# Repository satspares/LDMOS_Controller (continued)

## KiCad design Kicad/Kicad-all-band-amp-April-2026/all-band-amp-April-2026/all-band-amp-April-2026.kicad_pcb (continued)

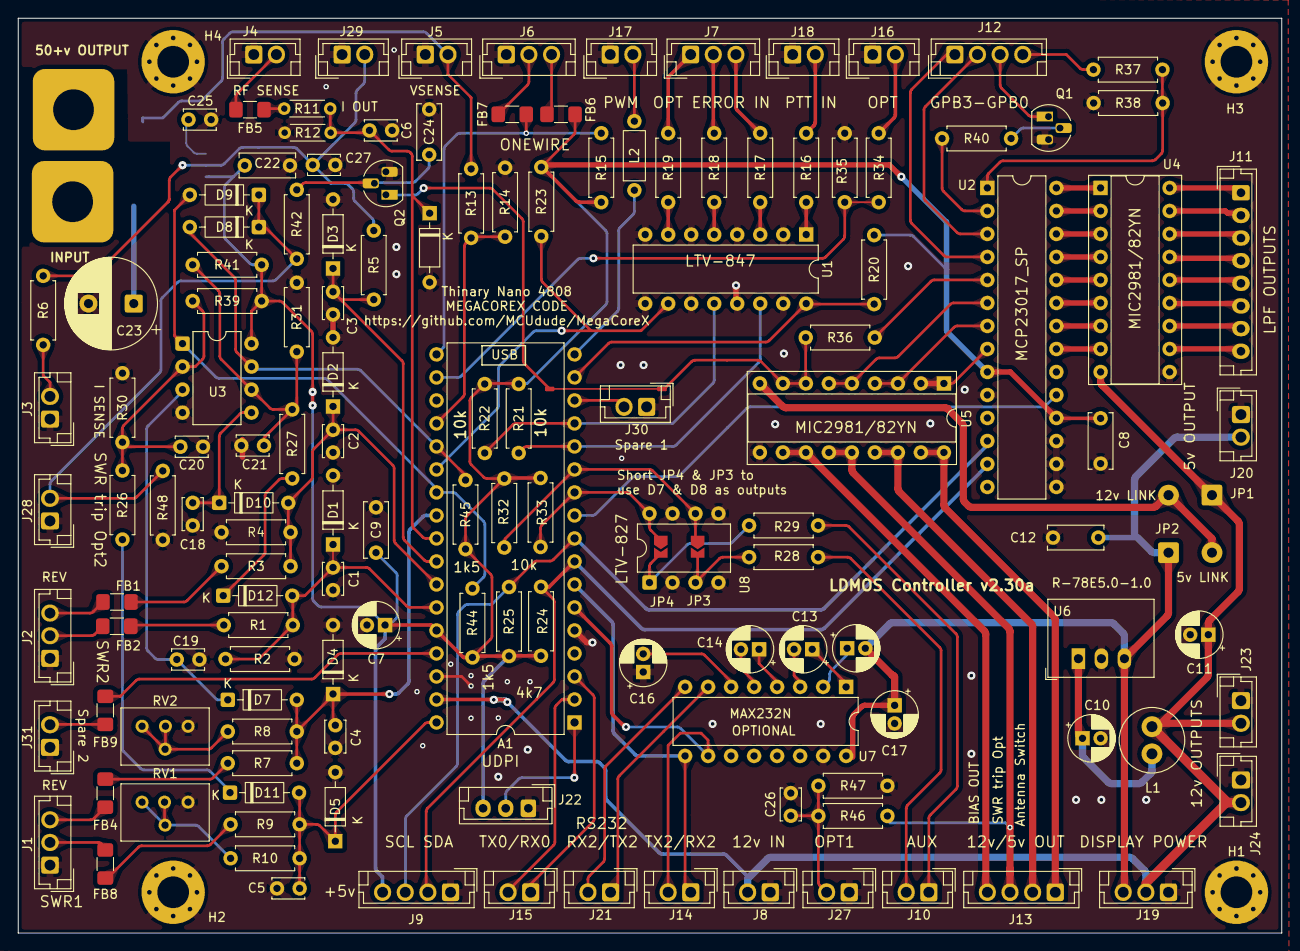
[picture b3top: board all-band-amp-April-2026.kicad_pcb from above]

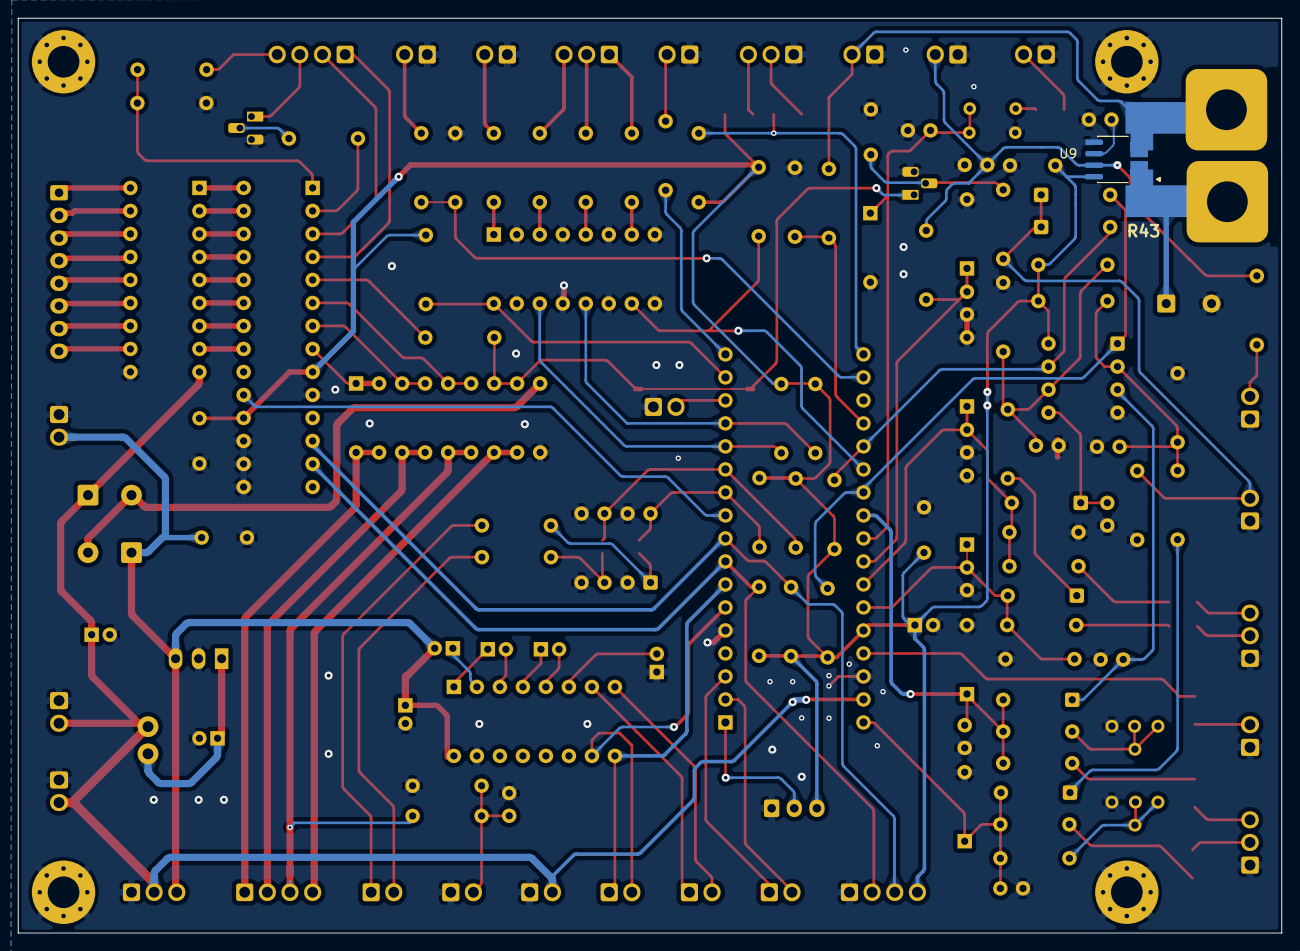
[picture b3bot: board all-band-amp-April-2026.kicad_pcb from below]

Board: 2 copper layers, 139.5 x 101.0 mm, 150 parts (2 on the bottom side), 117 nets.

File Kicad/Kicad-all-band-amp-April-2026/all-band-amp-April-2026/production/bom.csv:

Designator,Footprint,Quantity,Value,LCSC Part #
A1,DIP-34_W15.24mm,1,Arduino_Nano_Every-4808,
"C1, C18, C19, C2, C20, C21, C25, C26, C27, C3, C4, C5, C6",C_Disc_D3.4mm_W2.1mm_P2.50mm,13,10nf,
"C10, C17",CP_Radial_D5.0mm_P2.00mm,2,2.2uf,
"C11, C7",CP_Radial_D5.0mm_P2.00mm,2,10uf,
"C12, C22, C24, C8, C9",C_Disc_D6.0mm_W2.5mm_P5.00mm,5,100nf,
"C13, C14, C15, C16",CP_Radial_D5.0mm_P2.00mm,4,1uf,
C23,CP_Radial_D10.0mm_P5.00mm,1,10uf-220uf,
"D1, D2, D3, D4, D5, D6",D_DO-35_SOD27_P7.62mm_Horizontal,6,Zener 4.7v,
"D10, D11, D12, D7, D8, D9",D_DO-35_SOD27_P7.62mm_Horizontal,6,BAT85,
"FB1, FB2, FB4, FB5, FB6, FB7, FB8, FB9",1206,8,Ferrite,
J1,JST_EH_B3B-EH-A_1x03_P2.50mm_Vertical-mod2,1,SWR1,
J10,JST_EH_B2B-EH-A_1x02_P2.50mm_Vertical-Mod,1,Aux In,
J11,JST_EH_B8B-EH-A_1x08_P2.50mm_Vertical,1,LPF,
J12,JST_EH_B4B-EH-A_1x04_P2.50mm_Vertical-mod2,1,Digi In/Out,
J13,JST_EH_B4B-EH-A_1x04_P2.50mm_Vertical-mod2,1,12v/5v Outputs,
J14,JST_EH_B2B-EH-A_1x02_P2.50mm_Vertical-Mod,1,TX2/RX2,
J15,JST_EH_B2B-EH-A_1x02_P2.50mm_Vertical-Mod,1,TX0/RX0,
"J16, J5",JST_EH_B2B-EH-A_1x02_P2.50mm_Vertical-Mod,2,50v In.,
J17,JST_EH_B2B-EH-A_1x02_P2.50mm_Vertical-Mod,1,PWM Out,
J18,JST_EH_B2B-EH-A_1x02_P2.50mm_Vertical-Mod,1,PTT IN,
J19,JST_EH_B3B-EH-A_1x03_P2.50mm_Vertical-mod2,1,DISPLAY POWER,
J2,JST_EH_B3B-EH-A_1x03_P2.50mm_Vertical-mod2,1,SWR2,
J20,JST_EH_B2B-EH-A_1x02_P2.50mm_Vertical-Mod,1,5V Output,
J21,JST_EH_B2B-EH-A_1x02_P2.50mm_Vertical-Mod,1,RS232,
J22,JST_EH_B3B-EH-A_1x03_P2.50mm_Vertical,1,UDPI,
"J23, J24",JST_EH_B2B-EH-A_1x02_P2.50mm_Vertical-Mod,2,12v Output,
"J27, J28, J29, J30, J31",JST_EH_B2B-EH-A_1x02_P2.50mm_Vertical-Mod,5,SWR trip out,
J3,JST_EH_B2B-EH-A_1x02_P2.50mm_Vertical-Mod,1,I opt Input,
J4,JST_EH_B2B-EH-A_1x02_P2.50mm_Vertical-Mod,1,RF In Level,
J6,JST_EH_B3B-EH-A_1x03_P2.50mm_Vertical-mod2,1,Temp,
J7,JST_EH_B3B-EH-A_1x03_P2.50mm_Vertical-mod2,1,Conn_01x03_Pin,
J8,JST_EH_B2B-EH-A_1x02_P2.50mm_Vertical-Mod,1,12v Input,
J9,JST_EH_B4B-EH-A_1x04_P2.50mm_Vertical-mod2,1,I2c Output,
JP1,SolderWire-0.5sqmm_1x02_P4.8mm_D0.9mm_OD2.3mm,1,Jumper 12v,
JP2,SolderWire-0.5sqmm_1x02_P4.8mm_D0.9mm_OD2.3mm,1,Jumper 5v,
"JP3, JP4",SolderJumper-2_P1.3mm_Open_TrianglePad1.0x1.5mm,2,Jumper_2_Open,
L1,L_Radial_D7.0mm_P3.00mm,1,68uh,
L2,L_Axial_L5.3mm_D2.2mm_P7.62mm_Horizontal_Vishay_IM-1,1,560uh,
"Q1, Q2",TO-92_HandSolder,2,2n2222,
"R1, R44, R45, R46, R9",R_Axial_DIN0207_L6.3mm_D2.5mm_P7.62mm_Horizontal,5,1k5,
"R10, R8",R_Axial_DIN0207_L6.3mm_D2.5mm_P7.62mm_Horizontal,2,100r,
R11,R_Axial_DIN0204_L3.6mm_D1.6mm_P5.08mm_Horizontal,1,4k7,
R12,R_Axial_DIN0204_L3.6mm_D1.6mm_P5.08mm_Horizontal,1,470r,
R13,R_Axial_DIN0207_L6.3mm_D2.5mm_P7.62mm_Horizontal,1,100k,
R14,R_Axial_DIN0207_L6.3mm_D2.5mm_P7.62mm_Horizontal,1,5k1,
"R15, R24, R25",R_Axial_DIN0207_L6.3mm_D2.5mm_P7.62mm_Horizontal,3,4k7,
"R16, R42",R_Axial_DIN0207_L6.3mm_D2.5mm_P7.62mm_Horizontal,2,2k2,
"R17, R18, R19",R_Axial_DIN0207_L6.3mm_D2.5mm_P7.62mm_Horizontal,3,10r,
"R2, R4",R_Axial_DIN0207_L6.3mm_D2.5mm_P7.62mm_Horizontal,2,680r,
"R20, R21, R22, R23, R26, R27, R30, R31, R32, R33, R36",R_Axial_DIN0207_L6.3mm_D2.5mm_P7.62mm_Horizontal,11,10k,
"R28, R29",R_Axial_DIN0207_L6.3mm_D2.5mm_P7.62mm_Horizontal,2,470r,
"R3, R7",R_Axial_DIN0207_L6.3mm_D2.5mm_P7.62mm_Horizontal,2,1k5-3k3,
R34,R_Axial_DIN0207_L6.3mm_D2.5mm_P7.62mm_Horizontal,1,3k3,
"R35, R40, R47",R_Axial_DIN0207_L6.3mm_D2.5mm_P7.62mm_Horizontal,3,1k,
"R37, R38",R_Axial_DIN0207_L6.3mm_D2.5mm_P7.62mm_Horizontal,2,R,
"R39, R41",R_Axial_DIN0207_L6.3mm_D2.5mm_P7.62mm_Horizontal,2,220k-1M,
R43,CHSA3920R0003F-MOD,1,Shunt I>30a,
R48,R_Axial_DIN0207_L6.3mm_D2.5mm_P7.62mm_Horizontal,1,DNF,
R5,R_Axial_DIN0207_L6.3mm_D2.5mm_P7.62mm_Horizontal,1,470r or 47k opt,
R6,R_Axial_DIN0207_L6.3mm_D2.5mm_P7.62mm_Horizontal,1,47k opt,
"RV1, RV2",Potentiometer_Bourns_3299Y_Vertical,2,1k,
U1,DIP-16_W7.62mm,1,LTV-847,
U2,DIP-28_W7.62mm,1,MCP23017_SP,
U3,DIP-8_W7.62mm,1,LM393,
"U4, U5",DIP-18_W7.62mm_Socket,2,MIC2981/82YN,
U6,Converter_DCDC_RECOM_R-78E-0.5_THT,1,R-78E5.0-1.0,
U7,DIP-16_W7.62mm,1,MAX232N,
U8,DIP-8_W7.62mm,1,LTV-827,
U9,SOIC-8_3.9x4.9mm_P1.27mm,1,ACS712xLCTR-30A,

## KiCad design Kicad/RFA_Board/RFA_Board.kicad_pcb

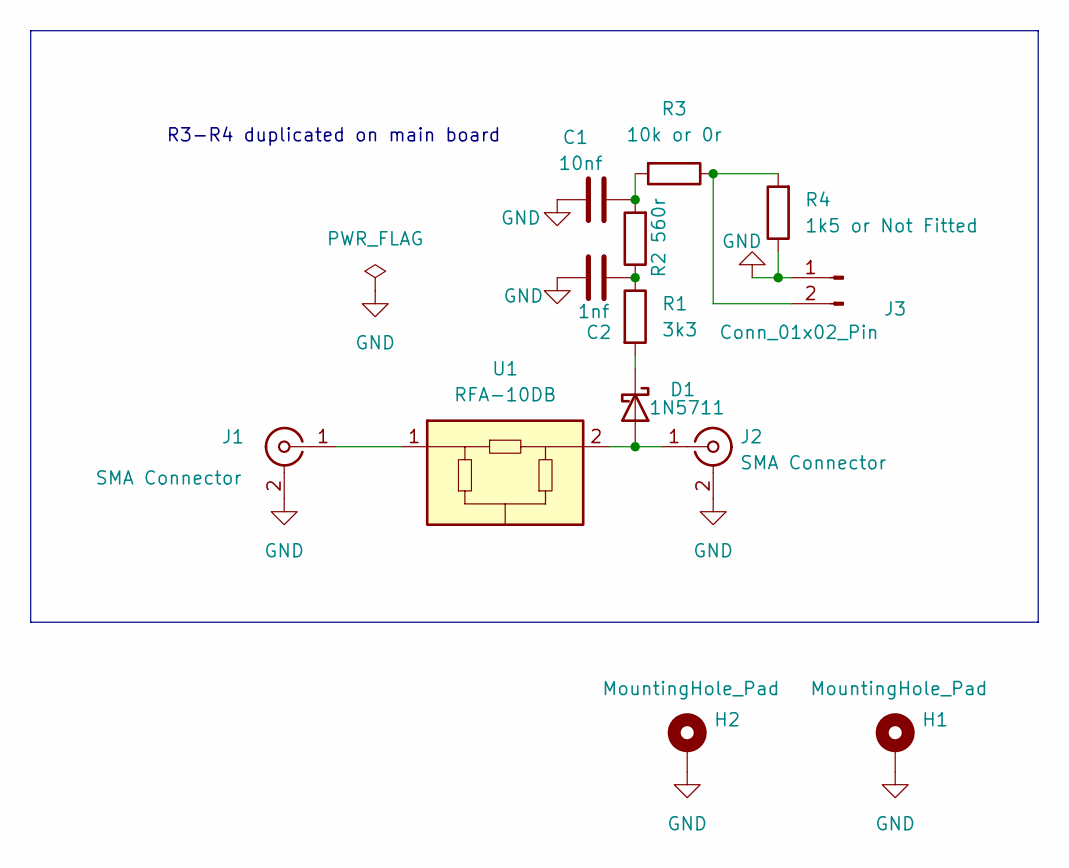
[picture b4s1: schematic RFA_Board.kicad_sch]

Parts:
C1: 10nf; C_1206_3216Metric_Pad1.33x1.80mm_HandSolder-mod
C2: 1nf; C_1206_3216Metric_Pad1.33x1.80mm_HandSolder-mod
D1: 1N5711; D_MELF-RM10_Universal_Handsoldering-mod
H1, H2: MountingHole_Pad; MountingHole_3.5mm_Pad_Via
J1, J2: SMA Connector; SMA_Molex_73251-2200_Horizontal_MOD
J3: Conn_01x02_Pin; SolderWirePad_1x02_SMD_12.5x8mm
R1: 3k3; R_1206_3216Metric_Pad1.30x1.75mm_HandSolder-mod
R2: 560r; R_1206_3216Metric_Pad1.30x1.75mm_HandSolder-mod
R3: 10k or 0r; R_1206_3216Metric_Pad1.30x1.75mm_HandSolder-mod
R4: 1k5 or Not Fitted; R_1206_3216Metric_Pad1.30x1.75mm_HandSolder-mod
U1: RFA-10DB; RFA Attenuator

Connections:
GND: C1.1, C2.1, H1.1 (1_1), H2.1 (1_1), J1.2 (Ext), J2.2 (Ext), J3.1, R4.1
unnamed: C1.2, R2.2, R3.2
unnamed: C2.2, R1.1, R2.1
unnamed: D1.2 (A), J2.1 (In), U1.2
unnamed: D1.1 (K), R1.2
unnamed: J1.1 (In), U1.1
unnamed: J3.2, R3.1, R4.2

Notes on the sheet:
R3-R4 duplicated on main board

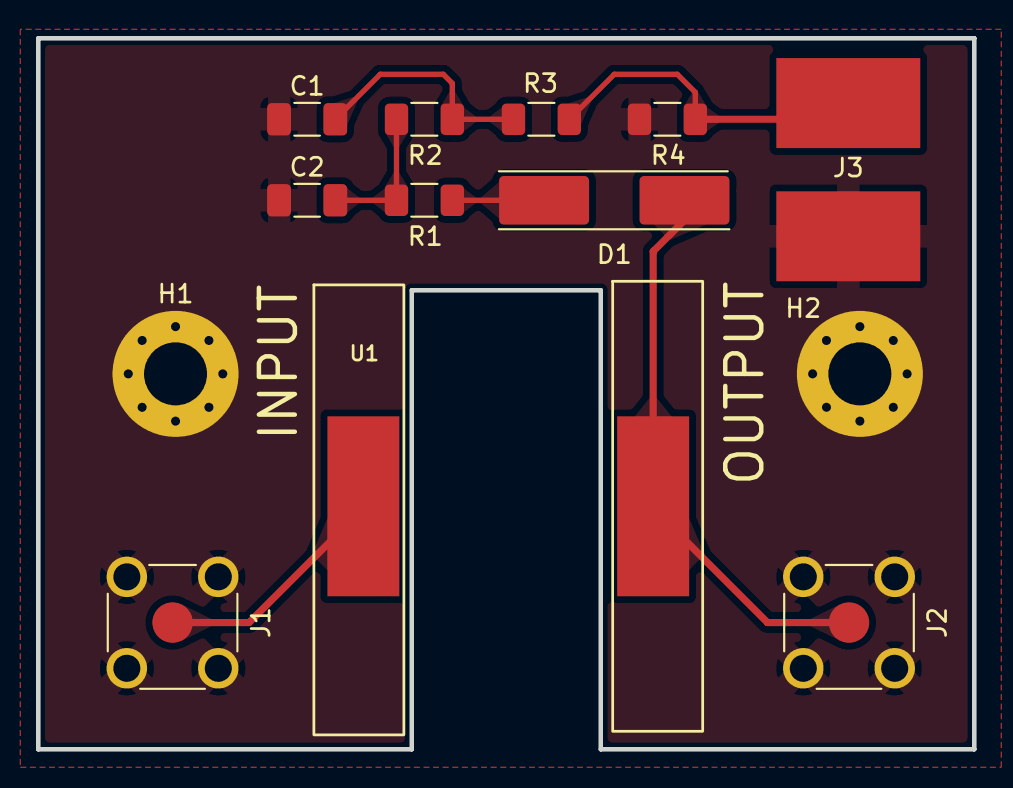
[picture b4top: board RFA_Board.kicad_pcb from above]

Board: 2 copper layers, 52.0 x 39.5 mm, 13 parts (0 on the bottom side), 7 nets.

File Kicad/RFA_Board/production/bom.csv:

Designator,Footprint,Quantity,Value,LCSC Part #
C1,1206,1,10nf,
C2,1206,1,1nf,
D1,D_MELF-RM10_Universal_Handsoldering,1,1N5711,
"J1, J2",SMA_Molex_73251-2200_Horizontal_MOD,2,SMA Connector,
J3,SolderWirePad_1x02_SMD_5x8mm,1,Conn_01x02_Pin,
R1,1206,1,3k3,
R2,1206,1,560r,
R3,1206,1,10k or 0r,
R4,1206,1,1k5 or Not Fitted,
U1,RFA Attenuator,1,RFA-10DB,

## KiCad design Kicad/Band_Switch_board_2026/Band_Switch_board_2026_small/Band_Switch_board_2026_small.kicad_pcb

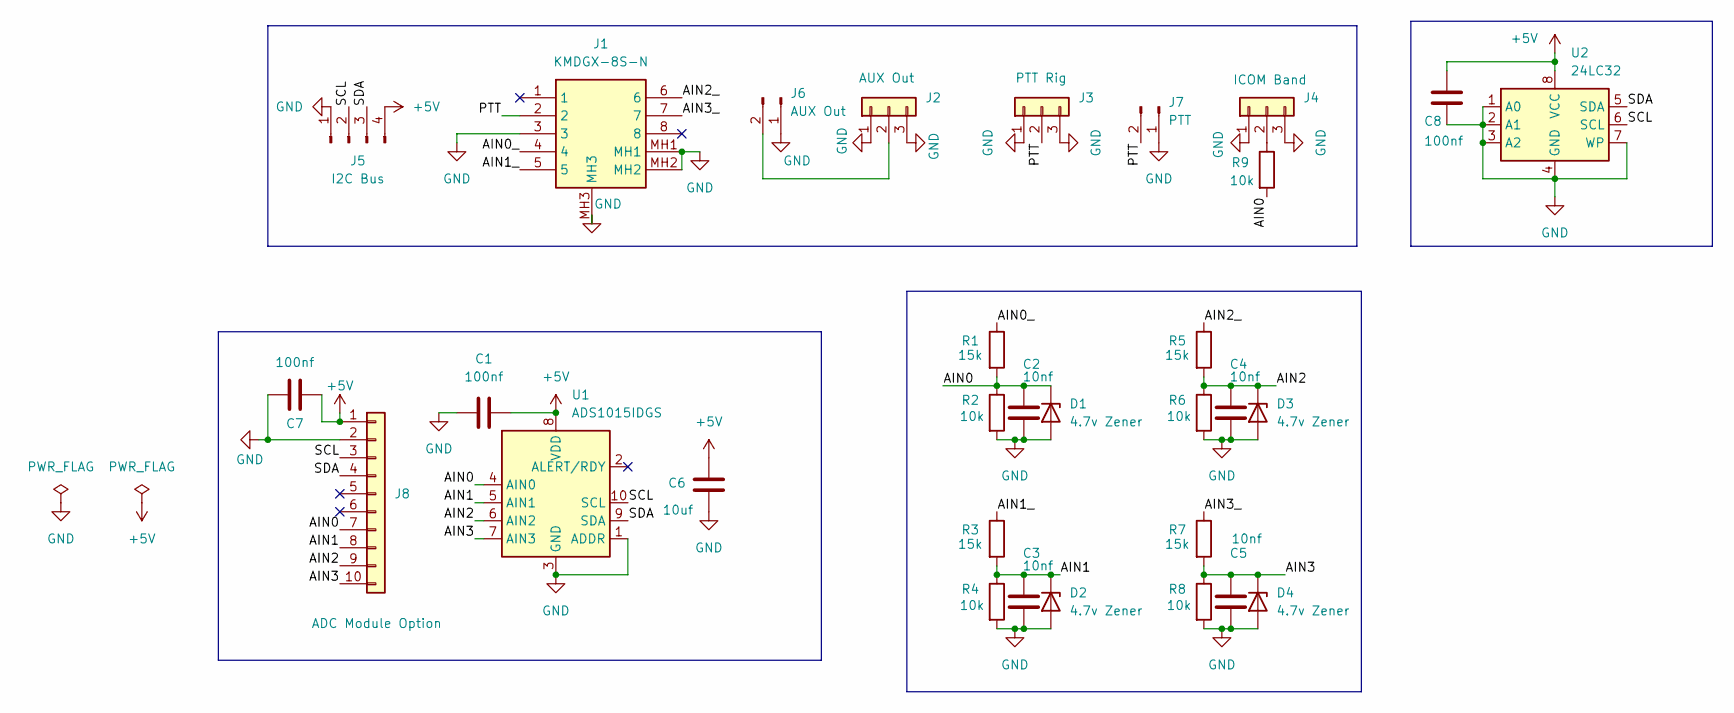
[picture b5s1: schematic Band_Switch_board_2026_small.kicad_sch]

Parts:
C1, C7, C8: 100nf; C_Disc_D6.0mm_W2.5mm_P5.00mm
C2, C3, C4, C5: 10nf; C_Disc_D3.4mm_W2.1mm_P2.50mm
C6: 10uf; CP_Radial_Tantal_D5.0mm_P2.50mm
D1, D2, D3, D4: 4.7v Zener; D_DO-35_SOD27_P7.62mm_Horizontal
J1: KMDGX-8S-N; KMDGX8SN; Mouser Part Number 806-KMDGX-8S-N
J2: AUX Out; BarrelJack__Horizontal_Band_Switch
J3: PTT Rig; BarrelJack__Horizontal_Band_Switch
J4: ICOM Band; BarrelJack__Horizontal_Band_Switch
J5: I2C Bus; JST_EH_B4B-EH-A_1x04_P2.50mm_Vertical
J6: AUX Out; JST_EH_B2B-EH-A_1x02_P2.50mm_Vertical
J7: PTT; JST_EH_B2B-EH-A_1x02_P2.50mm_Vertical
J8: ADC Module Option; PinHeader_1x10_P2.54mm_Vertical_ADC
R1, R3, R5, R7: 15k; R_Axial_DIN0207_L6.3mm_D2.5mm_P7.62mm_Horizontal
R2, R4, R6, R8, R9: 10k; R_Axial_DIN0207_L6.3mm_D2.5mm_P7.62mm_Horizontal
U1: ADS1015IDGS; TSSOP-10_3x3mm_P0.5mm
U2: 24LC32; DIP-8_W7.62mm_Socket

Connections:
+5V: C1.2, C6.1, C7.2, C8.2, J5.4, J8.1, U1.8 (VDD), U2.8 (VCC)
/AIN0: C2.1, D1.1 (K), J8.7, R1.2, R2.1, R9.2, U1.4 (AIN0)
/AIN0_: J1.4, R1.1
/AIN1: C3.1, D2.1 (K), J8.8, R3.2, R4.1, U1.5 (AIN1)
/AIN1_: J1.5, R3.1
/AIN2: C4.1, D3.1 (K), J8.9, R5.2, R6.1, U1.6 (AIN2)
/AIN2_: J1.6, R5.1
/AIN3: C5.1, D4.1 (K), J8.10, R7.2, R8.1, U1.7 (AIN3)
/AIN3_: J1.7, R7.1
/PTT: J1.2, J3.2, J7.2
/SCL: J5.2, J8.3, U1.10 (SCL), U2.6 (SCL)
/SDA: J5.3, J8.4, U1.9 (SDA), U2.5 (SDA)
GND: C1.1, C2.2, C3.2, C4.2, C5.2, C6.2, C7.1, C8.1, D1.2 (A), D2.2 (A), D3.2 (A), D4.2 (A), J1.3, J1.MH1, J1.MH2, J1.MH3, J2.1, J2.3, J3.1, J3.3, J4.1, J4.3, J5.1, J6.1, J7.1, J8.2, R2.2, R4.2, R6.2, R8.2, U1.1 (ADDR), U1.3 (GND), U2.1 (A0), U2.2 (A1), U2.3 (A2), U2.4 (GND), U2.7 (WP)
unnamed: J2.2, J6.2
unnamed: J4.2, R9.1

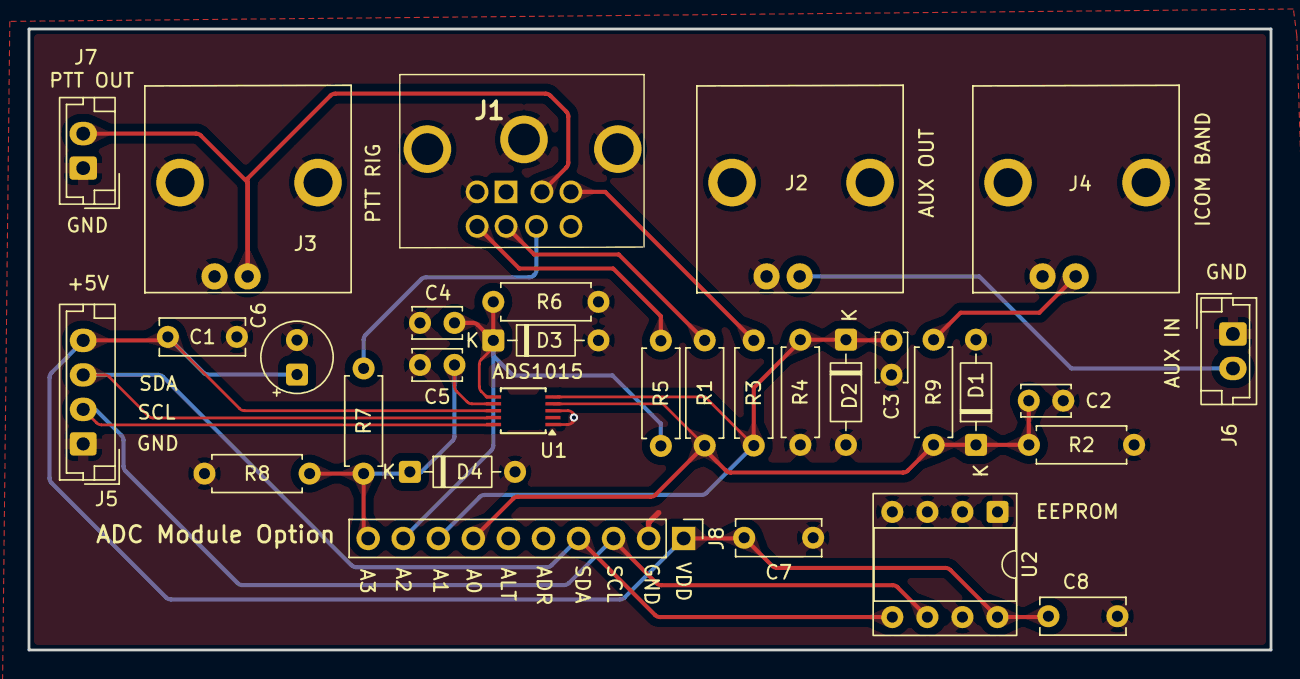
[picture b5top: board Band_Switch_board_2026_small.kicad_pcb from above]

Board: 2 copper layers, 90.0 x 45.0 mm, 31 parts (0 on the bottom side), 15 nets.

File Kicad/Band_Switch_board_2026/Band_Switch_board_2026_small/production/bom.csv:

Designator,Footprint,Quantity,Value,LCSC Part #
"C1, C7, C8",C_Disc_D6.0mm_W2.5mm_P5.00mm,3,100nf,
"C2, C3, C4, C5",C_Disc_D3.4mm_W2.1mm_P2.50mm,4,10nf,
C6,CP_Radial_Tantal_D5.0mm_P2.50mm,1,10uf,
"D1, D2, D3, D4",D_DO-35_SOD27_P7.62mm_Horizontal,4,4.7v Zener,
J1,KMDGX8SN,1,KMDGX-8S-N,
J2,BarrelJack__Horizontal_Band_Switch,1,AUX Out,
J3,BarrelJack__Horizontal_Band_Switch,1,PTT Rig,
J4,BarrelJack__Horizontal_Band_Switch,1,ICOM Band,
J5,JST_EH_B4B-EH-A_1x04_P2.50mm_Vertical,1,I2C Bus,
J6,JST_EH_B2B-EH-A_1x02_P2.50mm_Vertical,1,AUX Out,
J7,JST_EH_B2B-EH-A_1x02_P2.50mm_Vertical,1,PTT,
J8,PinHeader_1x10_P2.54mm_Vertical_ADC,1,ADC Module Option,
"R1, R3, R5, R7",R_Axial_DIN0207_L6.3mm_D2.5mm_P7.62mm_Horizontal,4,15k,
"R2, R4, R6, R8, R9",R_Axial_DIN0207_L6.3mm_D2.5mm_P7.62mm_Horizontal,5,10k,
U1,TSSOP-10_3x3mm_P0.5mm,1,ADS1015IDGS,
U2,DIP-8_W7.62mm_Socket,1,24LC32,

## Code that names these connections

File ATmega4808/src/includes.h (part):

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createSafeString(MainText2,30," --- YOUR CALL --- ")

/* ======= SWR Progress Bar Max Display eg. 200=2.00 swr 300=3.00 swr or other swr value * 100 ======== */
const uint16_t swrRangeMax = 250;  // 250 swr graph max is swr 2.50
const uint16_t powerRangeMax = 800; // Max Power graph range eg. 600=600 watts

/* ======= TX delay before tx needed for slow relays ======== */
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#endif


const uint16_t SWRColorChange = 16;         //change swr bar color on high swr (swr * 10 eg 16 = 1.6swr )
const uint16_t SWROriginalColor = 0xFC00;   // orange
const uint16_t SWRHighSWRColor = 0xF800;    //red

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// ************** Page 1 power calc page ***********
// Display controls
const uint16_t startPage_band_text = 0x5030;        //String 21 dec
const uint16_t startPage_swr_text = 0x5060;         //String 21 dec also used on page 4 swr calc
const uint16_t power_display_startPage = 0x2402;    // power in watt display
const uint16_t display_power_set_point = 0x2404; // power set point

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const uint8_t band4Mtr_switch =     0b00000001;

// MCP23017 port B pins
const uint8_t A600BIAS = 8;         //< pin GPB0 (1) of the MCP23017. via. resistor split
const uint8_t AUX_FAN_POWER = 9;    //< pin GPB1 (2) of the MCP23017. Transistor Base
const uint8_t FAN_POWER = 10;       //< pin GPB2 (3) of the MCP23017.
const uint8_t EN_I_BOARD = 11;      //< pin GPB3 (4) of the MCP23017.
const uint8_t BIAS12V = 12;         //< pin GPB4 (5) of the MCP23017.
const uint8_t SWR_TRIP = 13;        //< pin GPB5 (6) of the MCP23017.
const uint8_t ANTSWITCH = 14;       //< pin GPB6 (7) of the MCP23017.
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#define REF2        A6
#define ID_IN       A5
#define RFSENSE     A4
#define PTT         12 // new
#define LED_I       9  // DX-World errors
#define LED_PO      10 
#define LED_SWR     15 
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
